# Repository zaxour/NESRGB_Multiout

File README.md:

# NESRGB_Multiout
NES Multiout for use with Tim Worthington's NES RGB mod

Pads were laid out to match the NES RGB layout, removing the need to look at a wiring diagram and contort multiple wires to reach the correct pin.

**Top**

**Bottom**

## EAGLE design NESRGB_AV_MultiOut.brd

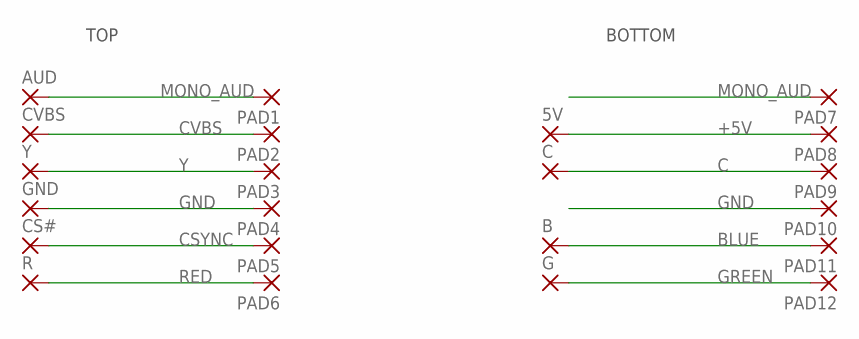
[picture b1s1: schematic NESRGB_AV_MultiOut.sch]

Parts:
5V: SMD2; SMD1,27-2,54
AUD: SMD2; SMD1,27-2,54
B: SMD2; SMD1,27-2,54
C: SMD2; SMD1,27-2,54
CS#: SMD2; SMD1,27-2,54
CVBS: SMD2; SMD1,27-2,54
G: SMD2; SMD1,27-2,54
GND: SMD2; SMD1,27-2,54
PAD1, PAD2, PAD3, PAD4, PAD5, PAD6, PAD7, PAD8, PAD9, PAD10, PAD11, PAD12: SMD_PADNIN_AV; SMD_NINAV
R: SMD2; SMD1,27-2,54
Y: SMD2; SMD1,27-2,54

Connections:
+5V: 5V.1, PAD8.1
BLUE: B.1, PAD11.1
C: C.1, PAD9.1
CSYNC: CS#.1, PAD5.1
CVBS: CVBS.1, PAD2.1
GND: GND.1, PAD4.1, PAD10.1
GREEN: G.1, PAD12.1
MONO_AUD: AUD.1, PAD1.1, PAD7.1
RED: PAD6.1, R.1
Y: PAD3.1, Y.1

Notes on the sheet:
TOP
BOTTOM

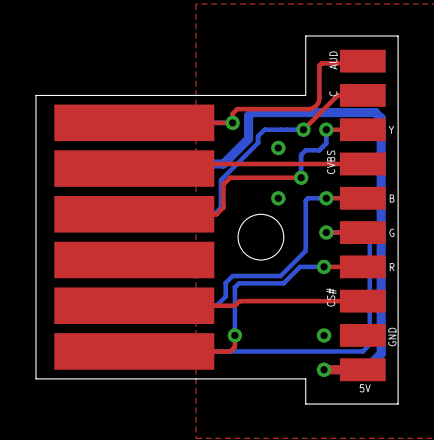
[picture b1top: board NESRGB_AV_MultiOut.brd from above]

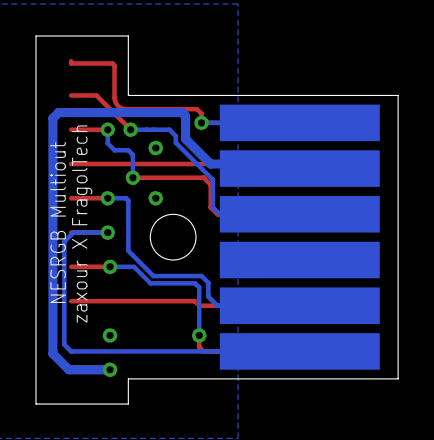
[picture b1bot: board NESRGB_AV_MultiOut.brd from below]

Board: 2 copper layers, 20.1 x 20.4 mm, 22 parts (6 on the bottom side), 10 nets.

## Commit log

2022-04-15 Add Images
2022-04-15 Update README with images
